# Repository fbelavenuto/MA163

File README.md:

# MA163

Interface Paralela Microdigital para TK3000//e

Foi realizado uma engenharia reversa na interface paralela da Microdigital (MA163) para TK3000//e. O esquema da interface foi recriado junto com o roteamento da placa original, podendo assim ser produzido placas que funcionam como a original.

O manual original da interface digitalizado foi encontrado neste [link](http://www.apple-iigs.info/doc/fichiers/TK3000%20IIe%20Super%20parallel%20card.pdf), uma cópia do arquivo está neste repositório.

# Pastas

`Common` possui os binários das ROMs, seus *disassemblys* e uma cópia do manual original digitalizado.

Dentro da pasta [`Rev1`](Rev1) há três subpastas com os nomes `Docs`, `Eagle` e `Gerber`. O esquema elétrico em PDF, imagens, lista de materiais, etc, estão em `Docs`. Na subpasta *Eagle* há os arquivos originais para a versão 9 do software Autodesk Eagle. Para a confecção das placas há os arquivos em formato gerber na pasta `Gerber` que podem ser enviados para uma empresa de fabricação de PCBs.

# Montagem

A lista de material pode ser encontrada [aqui](Rev1/Docs/Lista%20material.md).

Para facilitar a montagem abra o arquivo [ibom.html](Rev1/Docs/ibom.html) localmente ou acesse [este link](https://fbelavenuto.github.io/pages/MA163-Rev1-ibom.html) para visualizar os componentes e seus lugares na placa. Criado com o projeto [InteractiveHtmlBom](https://github.com/openscopeproject/InteractiveHtmlBom), linha de comando: `generate_interactive_bom --highlight-pin1 all --blacklist-empty-val MA163.brd`

Soquetes para os CIs não estão na lista de material mas são altamente recomendados para facilitar futuras manutenções.

Há a opção de usar uma rede resistiva RN1 ou usar os resistores R8 a R17 no seu lugar.

A montagem das memórias dinâmicas são opcionais. Elas são utilizadas como buffer para liberar o micro antes de terminar a impressão. Sem as memórias o micro fica "travado" até terminar a impressão. Podem ser usadas memórias 4464 para ter um buffer maior de 64KB.

# Disassembly

Foi efetuado o disassembly nas duas ROMs da interface, uma ROM é para o Apple-2 e outra ROM é para o Z80. Por enquanto não foi entendido totalmente as funções mas a maioria das coisas principais foram entendidas e comentadas. Para estes trabalhos foi utilizado a versão 6.1 Pro do software IDA da Hex-Rays.

# Observações

É recomendado a fabricação com finalização ENIG ou ouro no conector Edge para mais durabilidade.

O jumper de solda da placa não precisa ser soldado, este jumper não tem utilidade pois se mudado desabilita a saída de dados para a impressora, tornando a interface inútil!

# Curiosidades

A ROM do Apple-2 não é linear! O pino A6 desta ROM é invertido e controlado pelo Z80 e /DEVSEL, sendo assim o código que aparece para o Apple-2 muda dinamicamente. O Z80 quando escreve no endereço $5000 define o sinal FLAG_FW em 1. Quando o firmware do Apple-2 escreve em $C0xx (ativando /DEVSEL) o sinal FLAG_FW vai para 0.

O sinal FLAG_FW se em 1 faz A6 ficar invertido quando o Apple-2 acessa de $Cx00 a $Cx7F e ao acessar $Cx80 a $CxFF o sinal A6 é mantido sempre em 1. Se FLAG_FW for 0 o sinal A6 fica invertido sempre.

No TK3000//e o status da tecla MODE aparece no pino `INTIN` do slot 1. Se MODE estiver desabilitado o pino `INTIN` fica em 1.

Para a leitura de flags o Z80 utiliza o opcode `IN A,(0)`, porém a operação de I/O não é decodificada! O truque é que os sinais são forçados no barramento de dados com resistores, assim ao executar o `IN` o Z80 deixa o barramento livre e os resistores forçam o sinal que é lido corretamente. O status da tecla MODE vai no pino D5, o sinal BUSY vai no pino D6 via resistor R2 e o sinal !FLAG_FW vai no pino D7 via resistor R4.

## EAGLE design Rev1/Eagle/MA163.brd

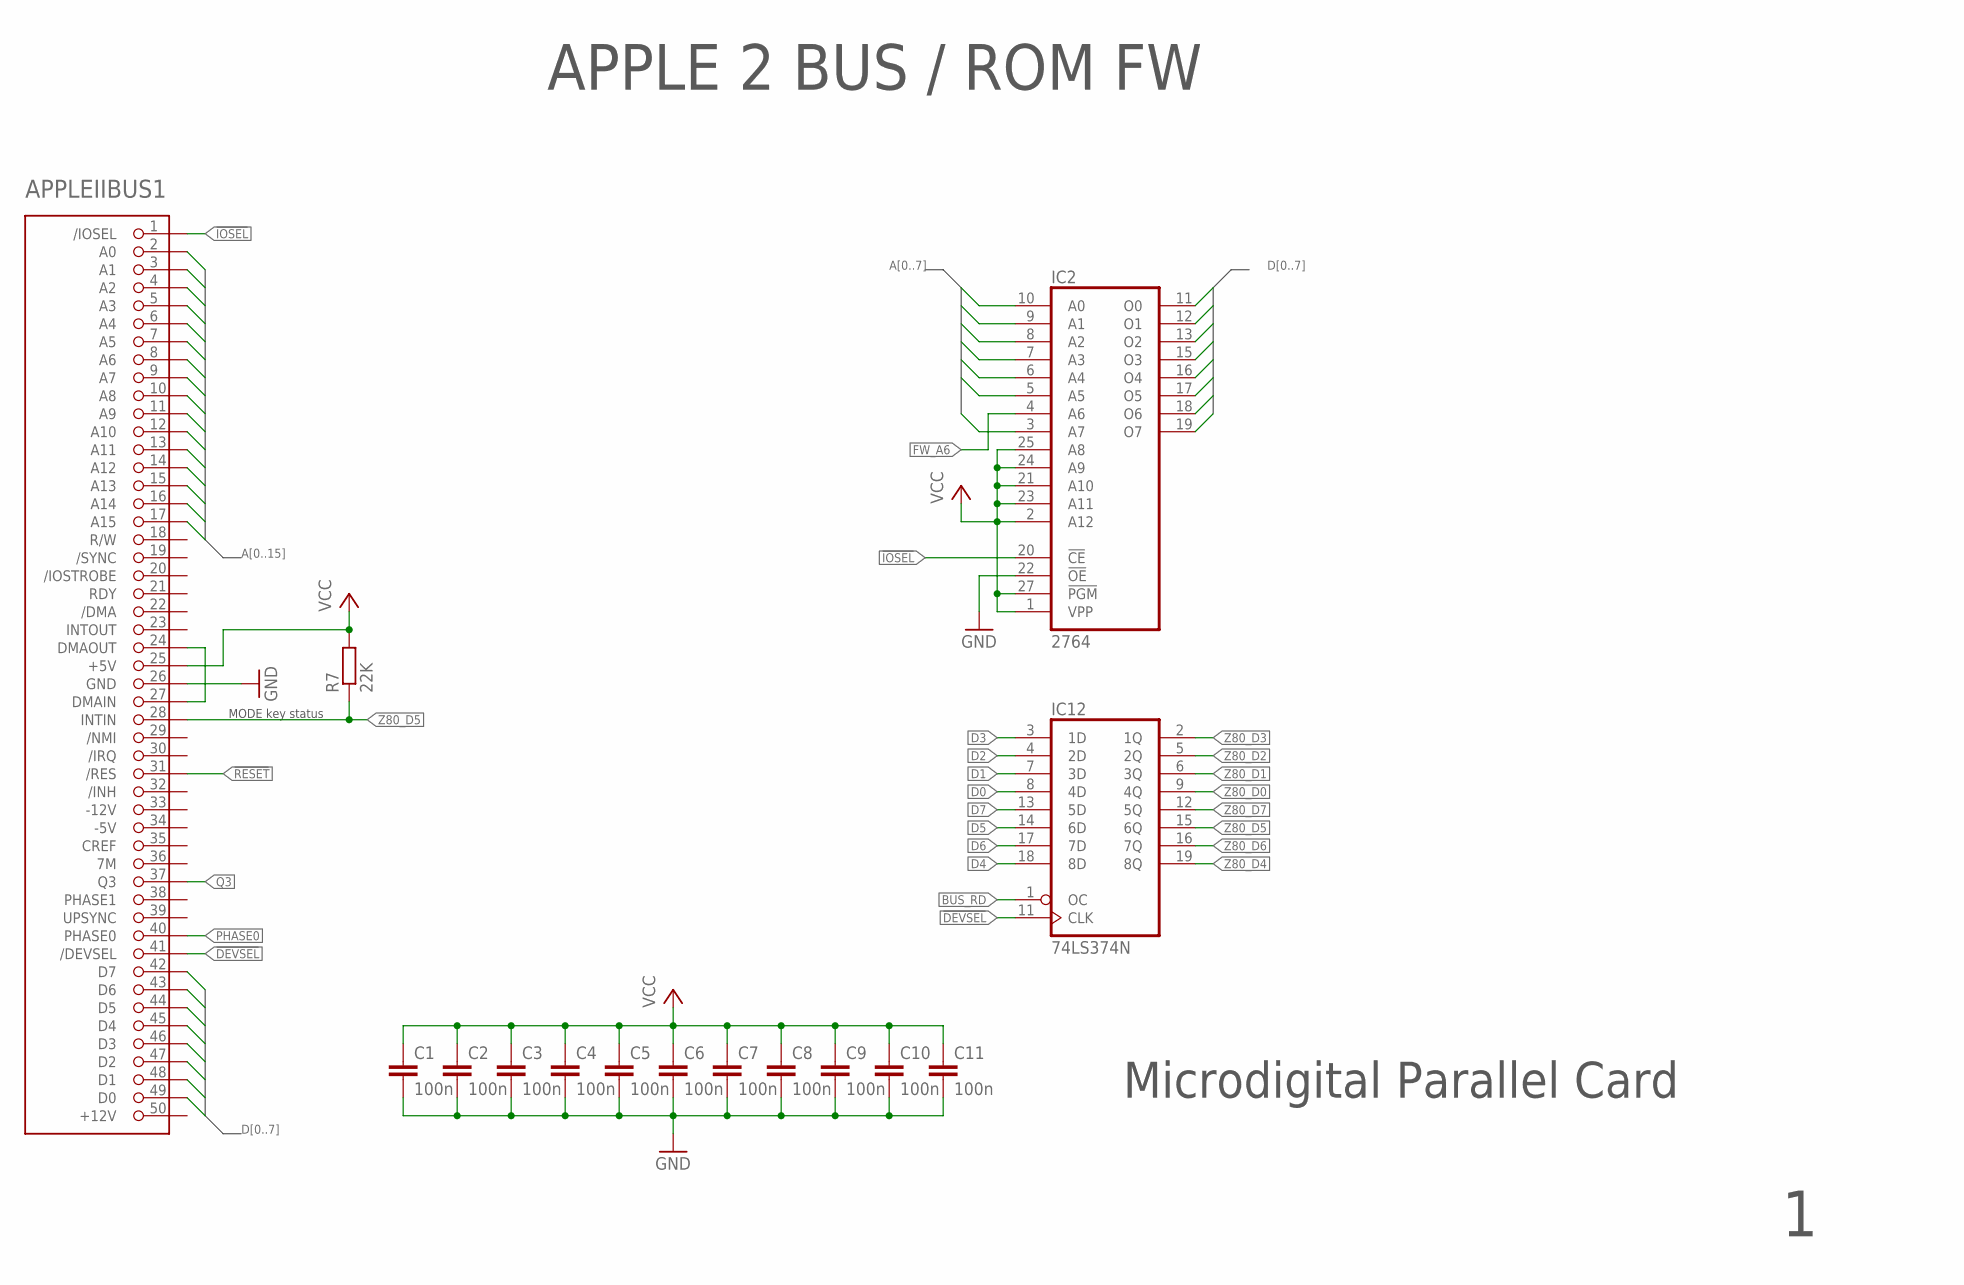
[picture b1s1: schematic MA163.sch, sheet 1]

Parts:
APPLEIIBUS1: APPLEIIBUS2X4; SLOT
C1, C2, C3, C4, C5, C6, C7, C8, C9, C10, C11: 100n; C050-025X075
IC2: 2764; DIL28
IC12: 74LS374N; DIL20
R7: 22K; 0207/12

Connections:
!DEVSEL: APPLEIIBUS1.41 (/DEVSEL), IC12.11 (CLK); also elsewhere on the board
!IOSEL: APPLEIIBUS1.1 (/IOSEL), IC2.20 (!CE)
!RESET: APPLEIIBUS1.31 (/RES); also elsewhere on the board
A0: APPLEIIBUS1.2 (A0), IC2.10 (A0)
A1: APPLEIIBUS1.3 (A1), IC2.9 (A1)
A2: APPLEIIBUS1.4 (A2), IC2.8 (A2)
A3: APPLEIIBUS1.5 (A3), IC2.7 (A3)
A4: APPLEIIBUS1.6 (A4), IC2.6 (A4)
A5: APPLEIIBUS1.7 (A5), IC2.5 (A5)
A6: APPLEIIBUS1.8 (A6); also elsewhere on the board
A7: APPLEIIBUS1.9 (A7), IC2.3 (A7); also elsewhere on the board
A8: APPLEIIBUS1.10 (A8)
A9: APPLEIIBUS1.11 (A9)
A10: APPLEIIBUS1.12 (A10)
A11: APPLEIIBUS1.13 (A11)
A12: APPLEIIBUS1.14 (A12)
A13: APPLEIIBUS1.15 (A13)
A14: APPLEIIBUS1.16 (A14)
A15: APPLEIIBUS1.17 (A15)
BUS_RD: IC12.1 (OC); also elsewhere on the board
D0: APPLEIIBUS1.49 (D0), IC2.11 (O0), IC12.8 (4D)
D1: APPLEIIBUS1.48 (D1), IC2.12 (O1), IC12.7 (3D)
D2: APPLEIIBUS1.47 (D2), IC2.13 (O2), IC12.4 (2D)
D3: APPLEIIBUS1.46 (D3), IC2.15 (O3), IC12.3 (1D)
D4: APPLEIIBUS1.45 (D4), IC2.16 (O4), IC12.18 (8D)
D5: APPLEIIBUS1.44 (D5), IC2.17 (O5), IC12.14 (6D)
D6: APPLEIIBUS1.43 (D6), IC2.18 (O6), IC12.17 (7D)
D7: APPLEIIBUS1.42 (D7), IC2.19 (O7), IC12.13 (5D)
FW_A6: IC2.4 (A6); also elsewhere on the board
GND: APPLEIIBUS1.26 (GND), C1.2, C2.2, C3.2, C4.2, C5.2, C6.2, C7.2, C8.2, C9.2, C10.2, C11.2, IC2.14 (GND), IC2.22 (!OE), IC12.10 (GND); also elsewhere on the board
unnamed: APPLEIIBUS1.24 (DMAOUT), APPLEIIBUS1.27 (DMAIN)
PHASE0: APPLEIIBUS1.40 (PHASE0); also elsewhere on the board
Q3: APPLEIIBUS1.37 (Q3); also elsewhere on the board
VCC: APPLEIIBUS1.25 (+5V), C1.1, C2.1, C3.1, C4.1, C5.1, C6.1, C7.1, C8.1, C9.1, C10.1, C11.1, IC2.1 (VPP), IC2.2 (A12), IC2.21 (A10), IC2.23 (A11), IC2.24 (A9), IC2.25 (A8), IC2.27 (!PGM), IC2.28 (VCC), IC12.20 (VCC), R7.2; also elsewhere on the board
Z80_D0: IC12.9 (4Q); also elsewhere on the board
Z80_D1: IC12.6 (3Q); also elsewhere on the board
Z80_D2: IC12.5 (2Q); also elsewhere on the board
Z80_D3: IC12.2 (1Q); also elsewhere on the board
Z80_D4: IC12.19 (8Q); also elsewhere on the board
Z80_D5: APPLEIIBUS1.28 (INTIN), IC12.15 (6Q), R7.1; also elsewhere on the board
Z80_D6: IC12.16 (7Q); also elsewhere on the board
Z80_D7: IC12.12 (5Q); also elsewhere on the board

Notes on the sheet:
Microdigital Parallel Card
APPLE 2 BUS / ROM FW
MODE key status

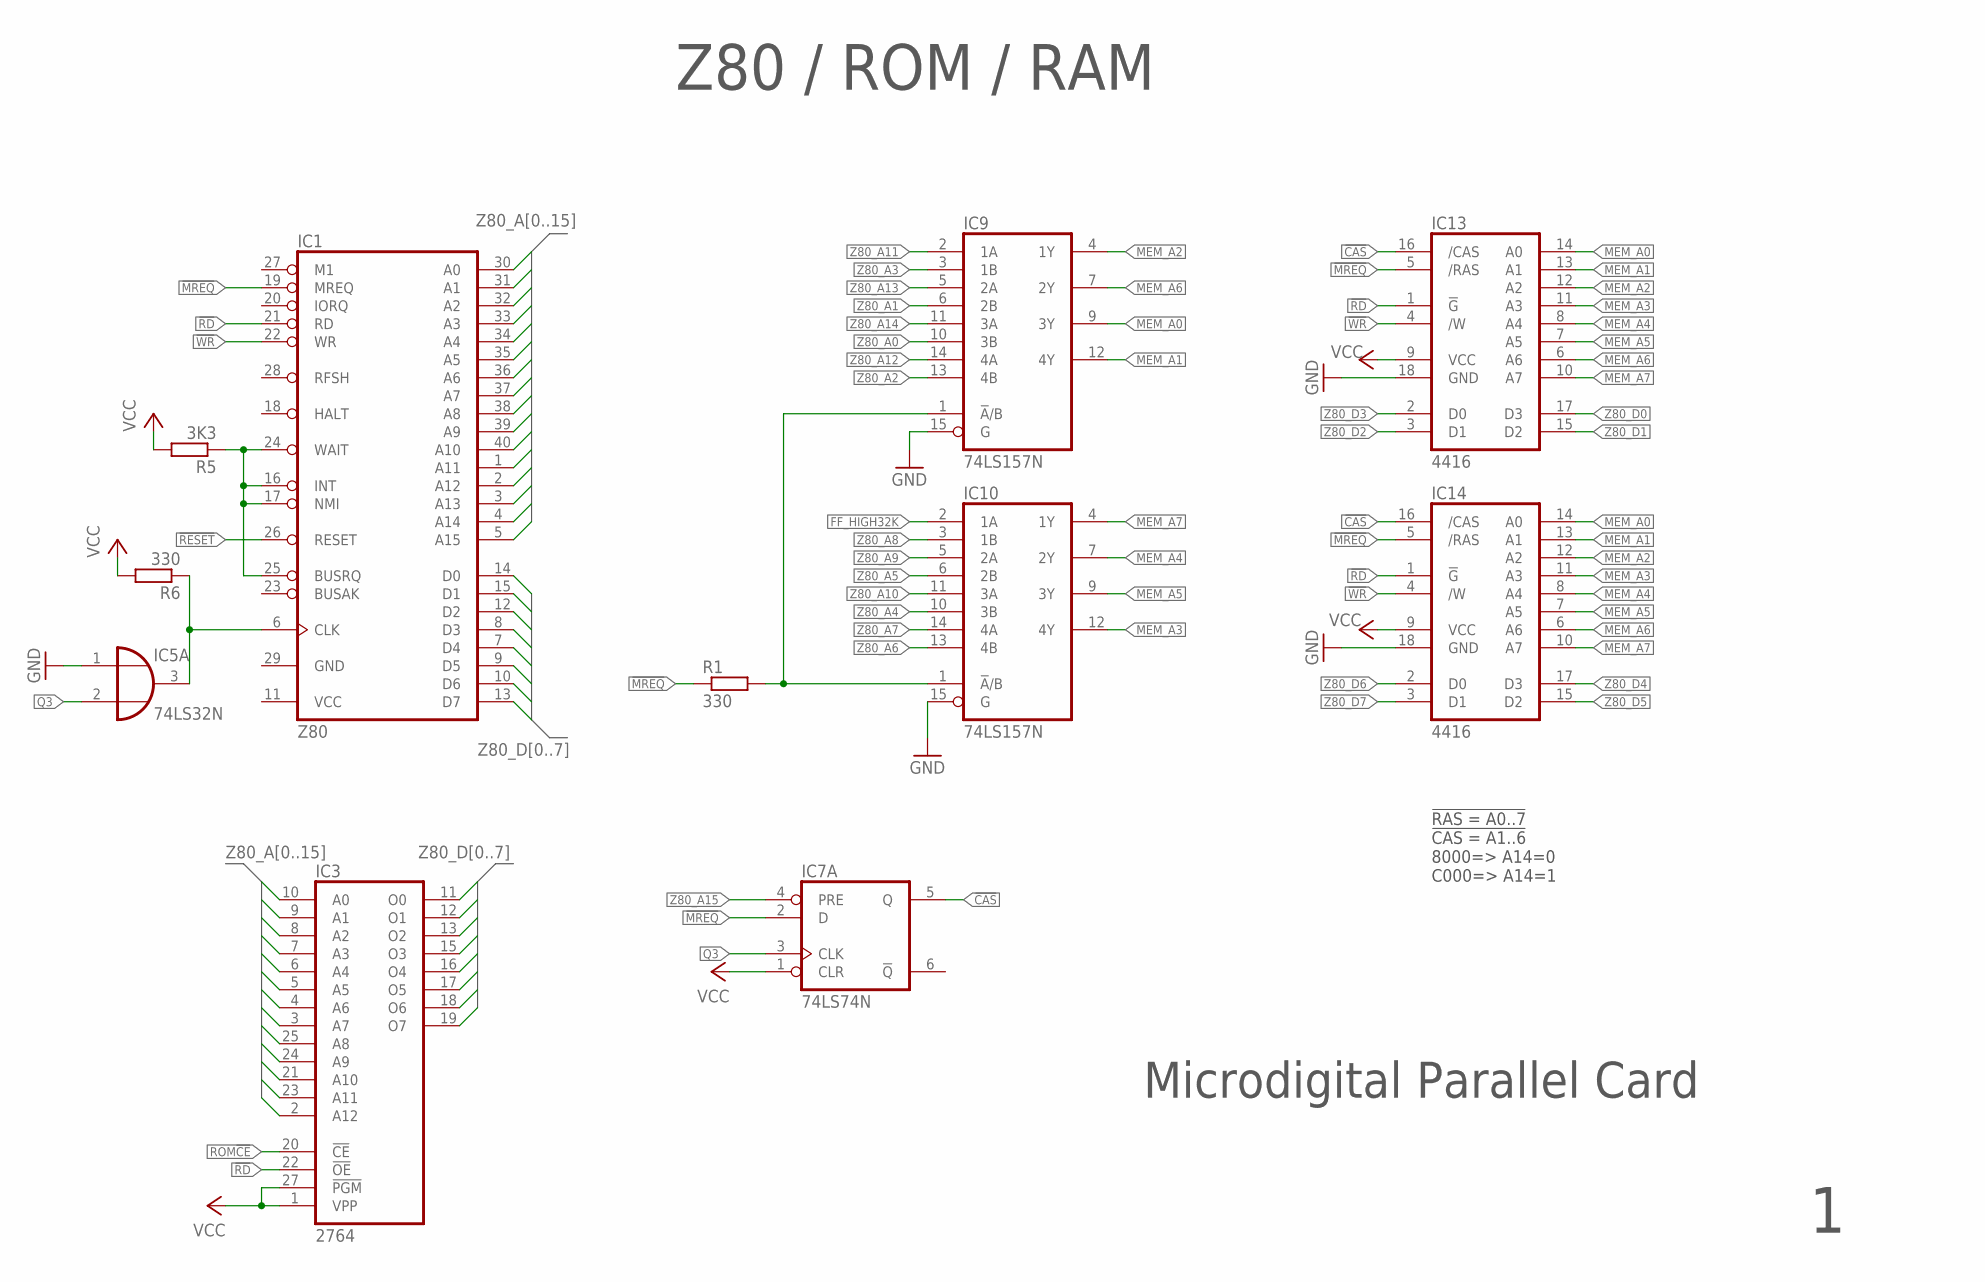
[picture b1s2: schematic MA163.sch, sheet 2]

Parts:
IC1: Z80; DIL40
IC3: 2764; DIL28
IC5: 74LS32N; DIL14
IC7: 74LS74N; DIL14
IC9, IC10: 74LS157N; DIL16
IC13, IC14: 4416; DIL18
R1, R6: 330; 0207/5V
R5: 3K3; 0207/5V

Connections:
!CAS: IC7.5 (Q), IC13.16 (/CAS), IC14.16 (/CAS)
!MREQ: IC1.19 (MREQ), IC7.2 (D), IC13.5 (/RAS), IC14.5 (/RAS), R1.1; also elsewhere on the board
!RD: IC1.21 (RD), IC3.22 (!OE), IC13.1 (!G), IC14.1 (!G)
!RESET: IC1.26 (RESET); also elsewhere on the board
!WR: IC1.22 (WR), IC13.4 (/W), IC14.4 (/W); also elsewhere on the board
!Z80_CLK: IC1.6 (CLK), IC5.3 (O), R6.1
FF_HIGH32K: IC10.2 (1A); also elsewhere on the board
GND: IC1.29 (GND), IC3.14 (GND), IC5.1 (I0), IC5.7 (GND), IC7.7 (GND), IC9.8 (GND), IC9.15 (G), IC10.8 (GND), IC10.15 (G), IC13.18 (GND), IC14.18 (GND); also elsewhere on the board
MEM_A0: IC9.9 (3Y), IC13.14 (A0), IC14.14 (A0)
MEM_A1: IC9.12 (4Y), IC13.13 (A1), IC14.13 (A1)
MEM_A2: IC9.4 (1Y), IC13.12 (A2), IC14.12 (A2)
MEM_A3: IC10.12 (4Y), IC13.11 (A3), IC14.11 (A3)
MEM_A4: IC10.7 (2Y), IC13.8 (A4), IC14.8 (A4)
MEM_A5: IC10.9 (3Y), IC13.7 (A5), IC14.7 (A5)
MEM_A6: IC9.7 (2Y), IC13.6 (A6), IC14.6 (A6)
MEM_A7: IC10.4 (1Y), IC13.10 (A7), IC14.10 (A7)
unnamed: IC1.16 (INT), IC1.17 (NMI), IC1.24 (WAIT), IC1.25 (BUSRQ), R5.1
unnamed: IC9.1 (!A!/B), IC10.1 (!A!/B), R1.2
Q3: IC5.2 (I1), IC7.3 (CLK); also elsewhere on the board
ROM!CE: IC3.20 (!CE); also elsewhere on the board
VCC: IC1.11 (VCC), IC3.1 (VPP), IC3.27 (!PGM), IC3.28 (VCC), IC5.14 (VCC), IC7.1 (CLR), IC7.14 (VCC), IC9.16 (VCC), IC10.16 (VCC), IC13.9 (VCC), IC14.9 (VCC), R5.2, R6.2; also elsewhere on the board
Z80_A0: IC1.30 (A0), IC3.10 (A0), IC9.10 (3B)
Z80_A1: IC1.31 (A1), IC3.9 (A1), IC9.6 (2B)
Z80_A2: IC1.32 (A2), IC3.8 (A2), IC9.13 (4B)
Z80_A3: IC1.33 (A3), IC3.7 (A3), IC9.3 (1B)
Z80_A4: IC1.34 (A4), IC3.6 (A4), IC10.10 (3B)
Z80_A5: IC1.35 (A5), IC3.5 (A5), IC10.6 (2B)
Z80_A6: IC1.36 (A6), IC3.4 (A6), IC10.13 (4B)
Z80_A7: IC1.37 (A7), IC3.3 (A7), IC10.14 (4A)
Z80_A8: IC1.38 (A8), IC3.25 (A8), IC10.3 (1B)
Z80_A9: IC1.39 (A9), IC3.24 (A9), IC10.5 (2A)
Z80_A10: IC1.40 (A10), IC3.21 (A10), IC10.11 (3A)
Z80_A11: IC1.1 (A11), IC3.23 (A11), IC9.2 (1A); also elsewhere on the board
Z80_A12: IC1.2 (A12), IC3.2 (A12), IC9.14 (4A); also elsewhere on the board
Z80_A13: IC1.3 (A13), IC9.5 (2A); also elsewhere on the board
Z80_A14: IC1.4 (A14), IC9.11 (3A); also elsewhere on the board
Z80_A15: IC1.5 (A15), IC7.4 (PRE); also elsewhere on the board
Z80_D0: IC1.14 (D0), IC3.11 (O0), IC13.17 (D3); also elsewhere on the board
Z80_D1: IC1.15 (D1), IC3.12 (O1), IC13.15 (D2); also elsewhere on the board
Z80_D2: IC1.12 (D2), IC3.13 (O2), IC13.3 (D1); also elsewhere on the board
Z80_D3: IC1.8 (D3), IC3.15 (O3), IC13.2 (D0); also elsewhere on the board
Z80_D4: IC1.7 (D4), IC3.16 (O4), IC14.17 (D3); also elsewhere on the board
Z80_D5: IC1.9 (D5), IC3.17 (O5), IC14.15 (D2); also elsewhere on the board
Z80_D6: IC1.10 (D6), IC3.18 (O6), IC14.2 (D0); also elsewhere on the board
Z80_D7: IC1.13 (D7), IC3.19 (O7), IC14.3 (D1); also elsewhere on the board

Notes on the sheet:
Microdigital Parallel Card
Z80 / ROM / RAM
!RAS = A0..7 !CAS = A1..6 8000=> A14=0 C000=> A14=1

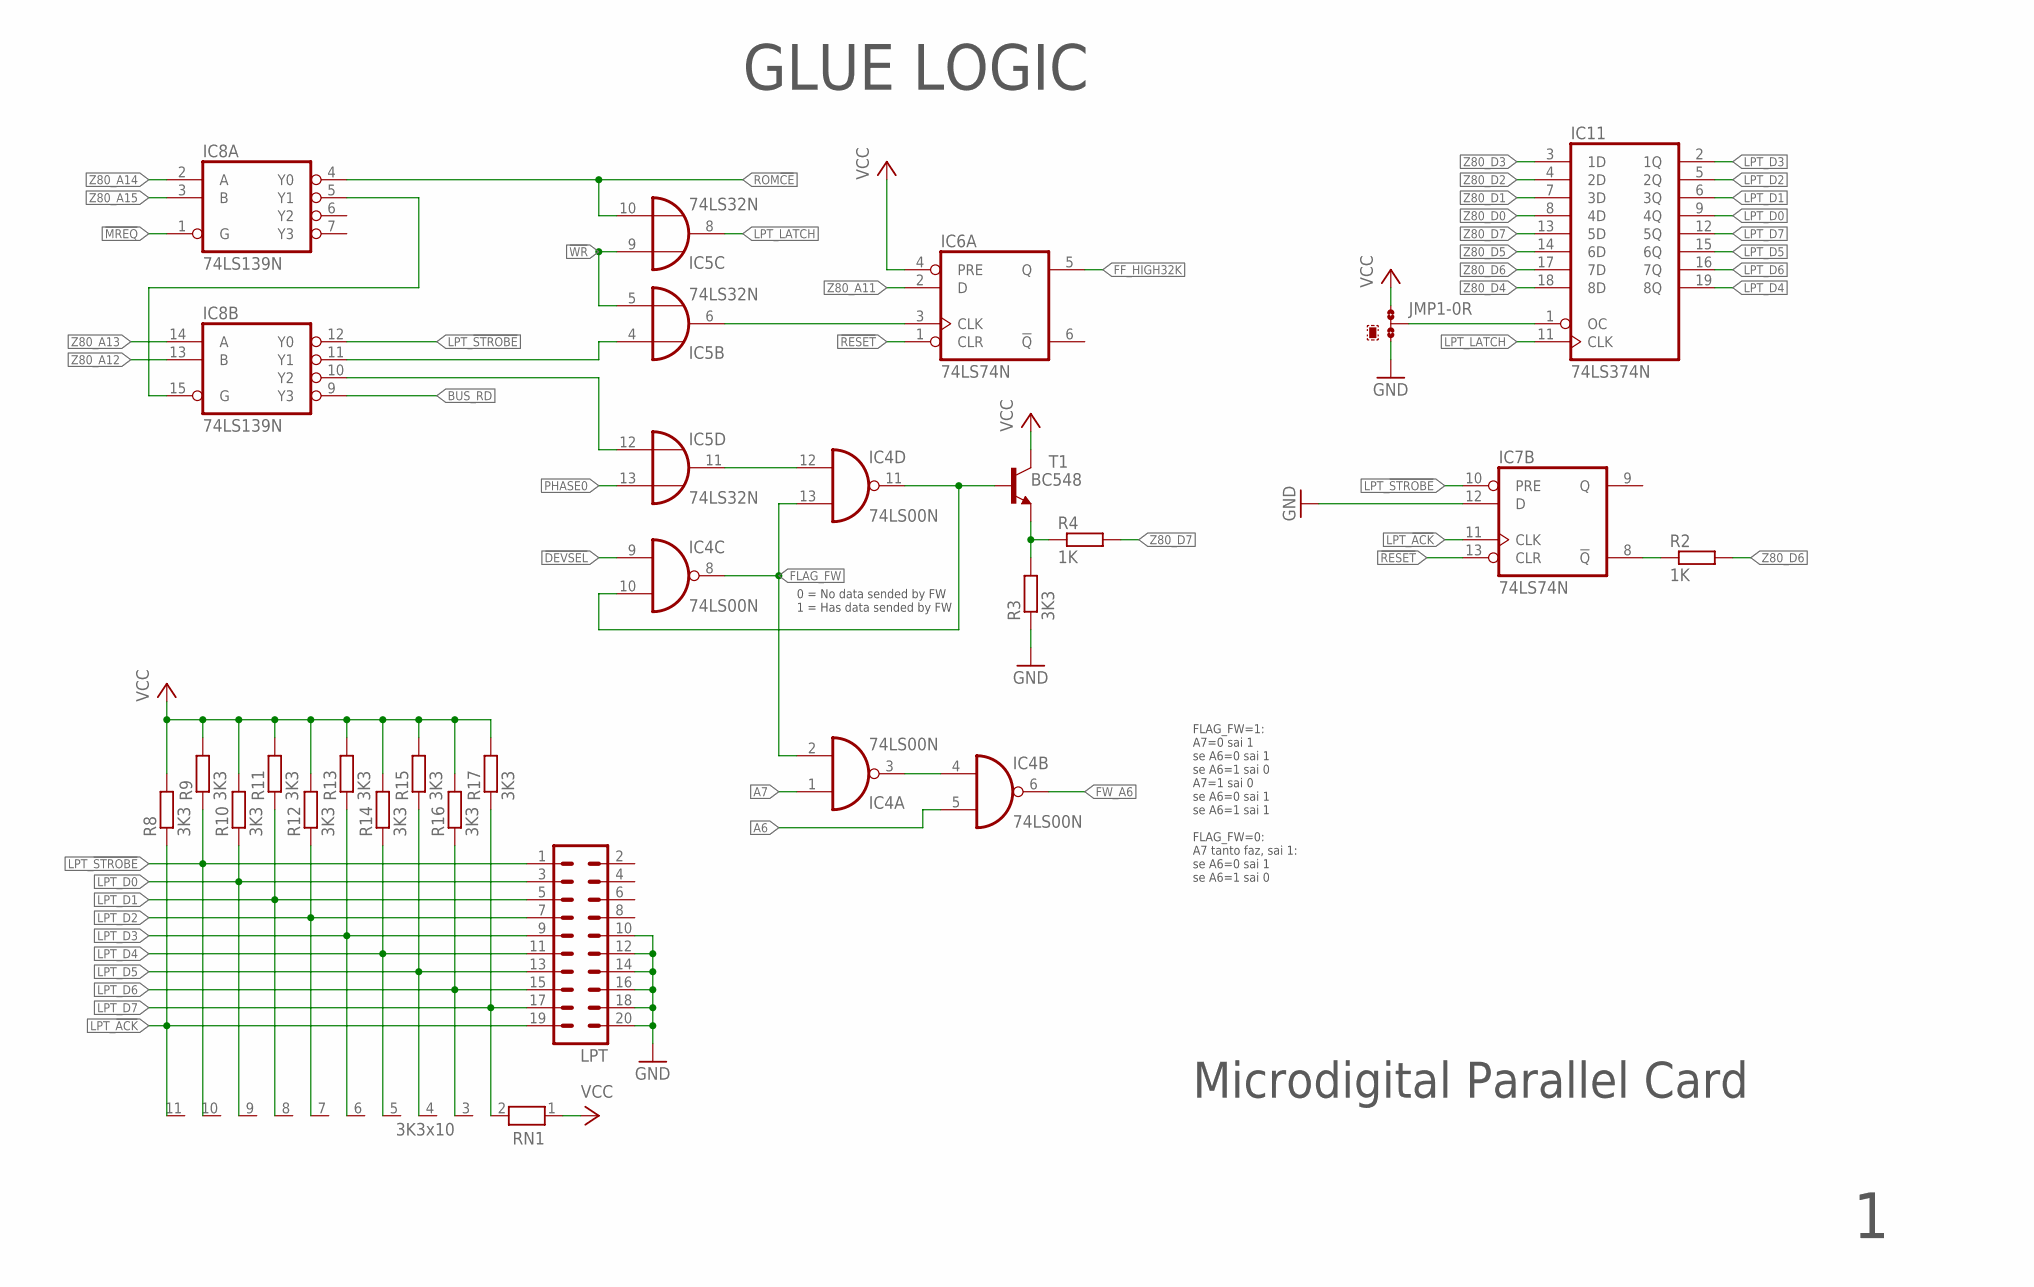
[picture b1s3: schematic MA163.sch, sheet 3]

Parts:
IC4: 74LS00N; DIL14
IC5: 74LS32N; DIL14
IC6, IC7: 74LS74N; DIL14
IC8: 74LS139N; DIL16
IC11: 74LS374N; DIL20
JMP1: 0R-JUMPB; B0R-JMP
LPT: MA10-2
R2, R4: 1K; 0207/5V
R3: 3K3; 0207/5V
R8, R9, R10, R11, R12, R13, R14, R15, R16, R17: 3K3; 0207/2V
RN1: 3K3x10; RN-11
T1: BC548; TO92L

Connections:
!DEVSEL: IC4.9 (I0); also elsewhere on the board
!MREQ: IC8.1 (G); also elsewhere on the board
!RESET: IC6.1 (CLR), IC7.13 (CLR); also elsewhere on the board
!WR: IC5.5 (I1), IC5.9 (I0); also elsewhere on the board
A6: IC4.5 (I1); also elsewhere on the board
A7: IC4.1 (I0); also elsewhere on the board
BUS_RD: IC8.9 (Y3); also elsewhere on the board
FF_HIGH32K: IC6.5 (Q); also elsewhere on the board
FLAG_FW: IC4.2 (I1), IC4.8 (O), IC4.13 (I1)
FW_A6: IC4.6 (O); also elsewhere on the board
GND: IC4.7 (GND), IC5.7 (GND), IC6.7 (GND), IC7.7 (GND), IC7.12 (D), IC8.8 (GND), IC11.10 (GND), JMP1.3, LPT.10, LPT.12, LPT.14, LPT.16, LPT.18, LPT.20, R3.1; also elsewhere on the board
LPT_!ACK: IC7.11 (CLK), LPT.19, R8.1, RN1.11
LPT_!STROBE: IC7.10 (PRE), IC8.12 (Y0), LPT.1, R9.1, RN1.10
LPT_D0: IC11.9 (4Q), LPT.3, R10.1, RN1.9
LPT_D1: IC11.6 (3Q), LPT.5, R11.1, RN1.8
LPT_D2: IC11.5 (2Q), LPT.7, R12.1, RN1.7
LPT_D3: IC11.2 (1Q), LPT.9, R13.1, RN1.6
LPT_D4: IC11.19 (8Q), LPT.11, R14.1, RN1.5
LPT_D5: IC11.15 (6Q), LPT.13, R15.1, RN1.4
LPT_D6: IC11.16 (7Q), LPT.15, R16.1, RN1.3
LPT_D7: IC11.12 (5Q), LPT.17, R17.1, RN1.2
LPT_LATCH: IC5.8 (O), IC11.11 (CLK)
unnamed: IC7.8 (!Q), R2.1
unnamed: R3.2, R4.1, T1.1 (E)
unnamed: IC5.4 (I0), IC8.11 (Y1)
unnamed: IC4.3 (O), IC4.4 (I0)
unnamed: IC8.5 (Y1), IC8.15 (G)
unnamed: IC11.1 (OC), JMP1.2
unnamed: IC4.10 (I1), IC4.11 (O), T1.2 (B)
unnamed: IC4.12 (I0), IC5.11 (O)
unnamed: IC5.6 (O), IC6.3 (CLK)
unnamed: IC5.12 (I0), IC8.10 (Y2)
PHASE0: IC5.13 (I1); also elsewhere on the board
ROM!CE: IC5.10 (I1), IC8.4 (Y0); also elsewhere on the board
VCC: IC4.14 (VCC), IC5.14 (VCC), IC6.4 (PRE), IC6.14 (VCC), IC7.14 (VCC), IC8.16 (VCC), IC11.20 (VCC), JMP1.1, R8.2, R9.2, R10.2, R11.2, R12.2, R13.2, R14.2, R15.2, R16.2, R17.2, RN1.1, T1.3 (C); also elsewhere on the board
Z80_A11: IC6.2 (D); also elsewhere on the board
Z80_A12: IC8.13 (B); also elsewhere on the board
Z80_A13: IC8.14 (A); also elsewhere on the board
Z80_A14: IC8.2 (A); also elsewhere on the board
Z80_A15: IC8.3 (B); also elsewhere on the board
Z80_D0: IC11.8 (4D); also elsewhere on the board
Z80_D1: IC11.7 (3D); also elsewhere on the board
Z80_D2: IC11.4 (2D); also elsewhere on the board
Z80_D3: IC11.3 (1D); also elsewhere on the board
Z80_D4: IC11.18 (8D); also elsewhere on the board
Z80_D5: IC11.14 (6D); also elsewhere on the board
Z80_D6: IC11.17 (7D), R2.2; also elsewhere on the board
Z80_D7: IC11.13 (5D), R4.2; also elsewhere on the board

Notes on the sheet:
GLUE LOGIC
FLAG_FW=1: A7=0 sai 1 se A6=0 sai 1 se A6=1 sai 0 A7=1 sai 0 se A6=0 sai 1 se A6=1 sai 1 FLAG_FW=0: A7 tanto faz, sai 1: se A6=0 sai 1 se A6=1 sai 0
0 = No data sended by FW 1 = Has data sended by FW
Microdigital Parallel Card

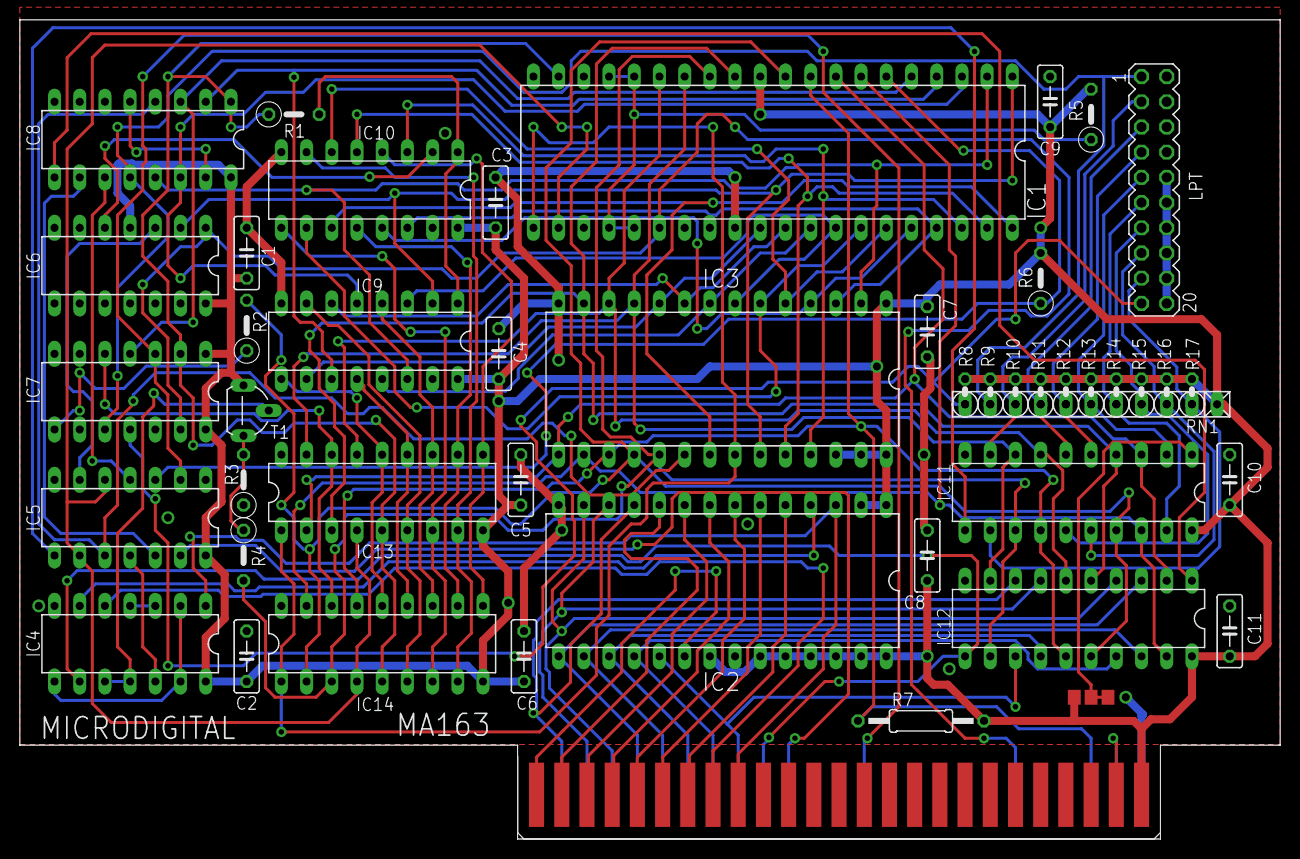
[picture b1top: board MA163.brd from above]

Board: 2 copper layers, 127.0 x 82.5 mm, 48 parts (1 on the bottom side), 89 nets.

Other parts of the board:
U$1: LOGO_FABIO_SILK_300MIL

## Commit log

2024-02-11 Primeiro envio
2024-02-15 Preparado board para roteamento
2024-02-15 Roteando
2024-02-15 Mais roteamento
2024-02-18 Roteamento finalizado
2024-02-20 Documentação
2024-02-20 Gerbers
2024-02-21 Adicionado link para Github Pages
2024-03-04 Adicionado silks da Microdigital e FBLabs
2024-04-12 Adicionado fotos do protótipo montado
